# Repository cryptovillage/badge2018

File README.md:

# badge2018

To buld the ESP32 firmware:

1. Install the ESP32 toolchain for your OS. You do not need to install the ESP-IDF -- that happens automatically in the next step.
  * For Linux: https://esp-idf.readthedocs.io/en/v3.2/get-started/linux-setup.html
  * For Windows: https://esp-idf.readthedocs.io/en/v3.2/get-started/windows-setup.html
  * For OSX: https://esp-idf.readthedocs.io/en/v3.2/get-started/macos-setup.html

2. Pull in the ESP-IDF, MicroPython, and other dependencies:
`git submodule update --init --recursive`

3. Build mpy_cross:
`cd firmware/esp32/components/micropython/micropython/mpy-cross/ && make && cd ../../../..`

4. Optionally configure the serial port that your badge appears on (under Serial Flasher Config):
`make menuconfig`

5. Build it:
`make -j5`

6. Flash it:
`make flash`

The EFM8 firmware has only been built inside Simplicity Studio.

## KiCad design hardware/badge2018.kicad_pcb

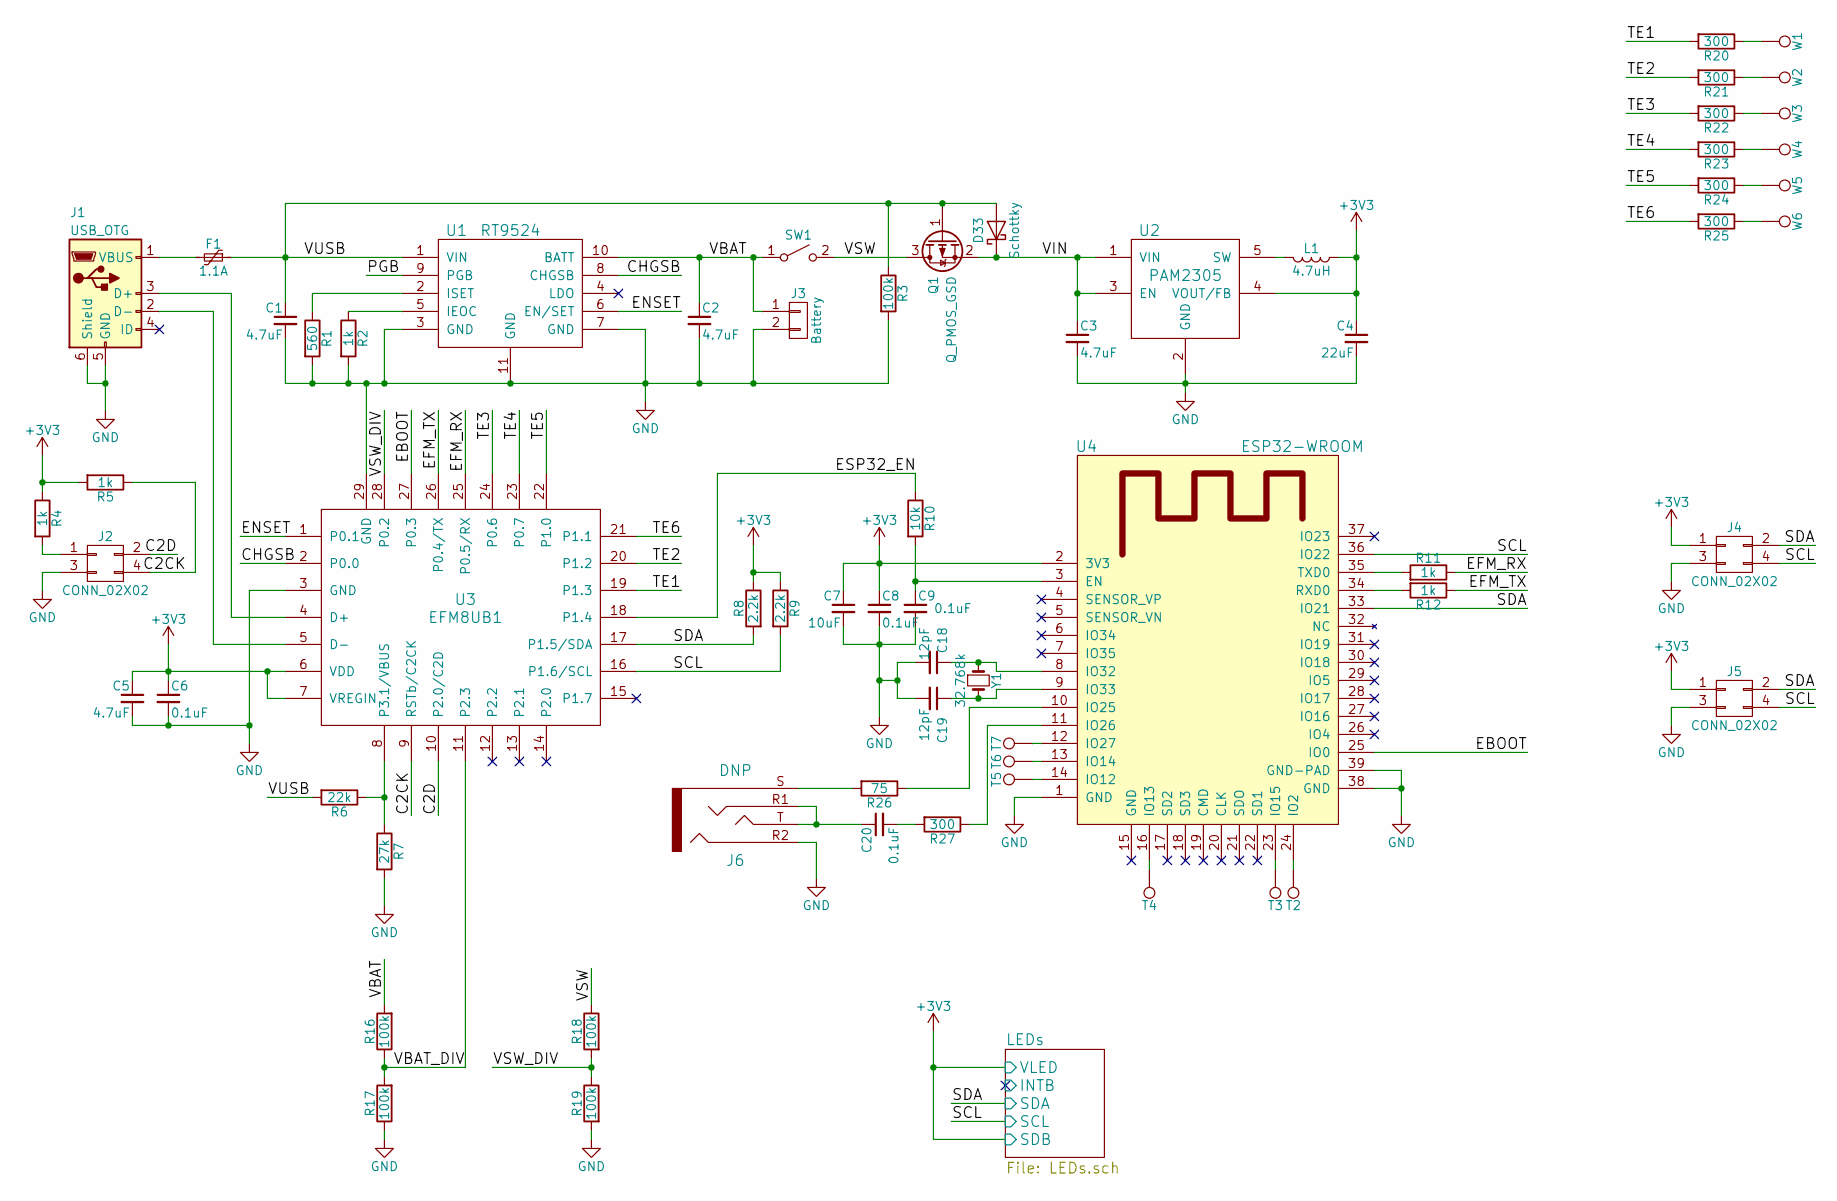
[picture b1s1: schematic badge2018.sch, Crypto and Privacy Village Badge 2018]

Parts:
C1, C2, C3, C5: 4.7uF; C_0603; Tolerance +/- 10%; Voltage 10V
C4: 22uF; C_0603; Tolerance +/- 10%; Voltage 10V
C6, C8, C9: 0.1uF; C_0603; Tolerance +/- 10%; Voltage 6.3V
C7: 10uF; C_0603; Tolerance +/- 10%; Voltage 10V
C18, C19: 12pF; C_0603; Tolerance +/- 10%; Voltage 6.3V
C20: 0.1uF; C_0603; Tolerance +/- 10%; Voltage 10V
D33: Schottky; D_SOD-323; MfgPartNum BAT20JFILM
F1: 1.1A; R_1210; Voltage 6V; MfgPartNum MF-USMF110-2
J1: USB_OTG; USB_Micro-B-cpv; MfgPartNum 10118192-0001LF
J2: CONN_02X02; Socket_Strip_Straight_2x02_TP
J3: Battery; JST_PH_SMD; MfgPartNum S2B-PH-SM4-TB(LF)(SN)
J4, J5: CONN_02X02; DC26_Shitty_Addon
J6: DNP; TRRS_jack; MfgPartNum SJ-43516-SMT-TR
L1: 4.7uH; R_0805
Q1: Q_PMOS_GSD; SOT-23; Voltage 30V; MfgPartNum DMG2307L-7
R1: 560; R_0603; Tolerance 1%
R2: 1k; R_0603; Tolerance 1%
R3: 100k; R_0603; Tolerance 5%
R4, R5, R11, R12: 1k; R_0603; Tolerance 5%
R6: 22k; R_0603; Tolerance 5%
R7: 27k; R_0603; Tolerance 5%
R8, R9: 2.2k; R_0603; Tolerance 5%
R10: 10k; R_0603; Tolerance 5%
R16, R17, R18, R19: 100k; R_0603; Tolerance 1%
R20, R21, R22, R23, R24: 300; R_0603; Tolerance 5%
R25, R27: 300; R_0603; Tolerance 1%
R26: 75; R_0603; Tolerance 1%
SW1: SPST; DPDT_SMD; Voltage 6V; MfgPartNum JS202011SCQN
T2, T3, T4, T5, T6, T7: TP; Measurement_Point_Round-SMD-Pad_Small
U1: RT9524; DFN-10-1EP_2x3mm_Pitch0.5mm; MfgPartNum RT9524GQW
U2: PAM2305; SOT-23-5; MfgPartNum PAM2305AAB330
U3: EFM8UB1; QFN-28-1EP_5x5mm_Pitch0.5mm; MfgPartNum EFM8UB10F16G-C-QFN28
U4: ESP32-WROOM; MfgPartNum ESP-WROOM-32
W1, W2, W3, W4, W5, W6: TP; Measurement_Point_Round-SMD-Pad_Small
Y1: 32.768k; abs25_crystal; MfgPartNum ABS25-32.768KHZ-T

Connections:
+3V3: C4.1, C5.1, C6.1, C7.1, C8.1, J4.1, J5.1, L1.1, R4.1, R5.2, R8.1, R9.1, U2.4 (VOUT/FB), U3.6 (VDD), U3.7 (VREGIN), U4.2 (3V3); also elsewhere on the board
/C2CK: J2.4, R5.1, U3.9 (RSTb/C2CK)
/C2D: J2.2, U3.10 (P2.0/C2D)
/CHGSB: U1.8 (CHGSB), U3.2 (P0.0)
/EBOOT: U3.27 (P0.3), U4.25 (IO0)
/EFM_RX: R11.1, U3.25 (P0.5/RX)
/EFM_TX: R12.1, U3.26 (P0.4/TX)
/ENSET: U1.6 (EN/SET), U3.1 (P0.1)
/ESP32_EN: R10.1, U3.18 (P1.4)
/PGB: U1.9 (PGB)
/SCL: J4.4, J5.4, R9.2, U3.16 (P1.6/SCL), U4.36 (IO22); also elsewhere on the board
/SDA: J4.2, J5.2, R8.2, U3.17 (P1.5/SDA), U4.33 (IO21); also elsewhere on the board
/TE1: R20.2, U3.19 (P1.3)
/TE2: R21.2, U3.20 (P1.2)
/TE3: R22.2, U3.24 (P0.6)
/TE4: R23.2, U3.23 (P0.7)
/TE5: R24.2, U3.22 (P1.0)
/TE6: R25.2, U3.21 (P1.1)
/VBAT: C2.1, J3.1, R16.2, SW1.1 (A), U1.10 (BATT)
/VBAT_DIV: R16.1, R17.2, U3.11 (P2.3)
/VIN: C3.1, D33.1 (K), Q1.2 (S), U2.1 (VIN), U2.3 (EN)
/VSW: Q1.3 (D), R18.1, SW1.2 (B)
/VSW_DIV: R18.2, R19.1, U3.28 (P0.2)
/VUSB: C1.1, D33.2 (A), F1.1, Q1.1 (G), R3.1, R6.2, U1.1 (VIN)
GND: C1.2, C2.2, C3.2, C4.2, C5.2, C6.2, C7.2, C8.2, C9.2, C18.2, C19.2, J1.5 (GND), J1.6 (Shield), J2.3, J3.2, J4.3, J5.3, J6.R2, R1.2, R2.2, R3.2, R7.2, R17.1, R19.2, U1.3 (GND), U1.7 (GND), U1.11 (GND), U2.2 (GND), U3.3 (GND), U3.29 (GND), U4.1 (GND), U4.38 (GND), U4.39 (GND-PAD); also elsewhere on the board
unnamed: C9.1, R10.2, U4.3 (EN)
unnamed: C18.1, U4.8 (IO32), Y1.1
unnamed: C19.1, U4.9 (IO33), Y1.2
unnamed: C20.1, J6.R1, J6.T
unnamed: C20.2, R27.2
unnamed: F1.2, J1.1 (VBUS)
unnamed: J1.2 (D-), U3.5 (D-)
unnamed: J1.3 (D+), U3.4 (D+)
unnamed: J2.1, R4.2
unnamed: J6.S, R26.2
unnamed: L1.2, U2.5 (SW)
unnamed: R1.1, U1.2 (ISET)
unnamed: R2.1, U1.5 (IEOC)
unnamed: R6.1, R7.1, U3.8 (P3.1/VBUS)
unnamed: R11.2, U4.35 (TXD0)
unnamed: R12.2, U4.34 (RXD0)
unnamed: R20.1, W1.1
unnamed: R21.1, W2.1
unnamed: R22.1, W3.1
unnamed: R23.1, W4.1
unnamed: R24.1, W5.1
unnamed: R25.1, W6.1
unnamed: R26.1, U4.10 (IO25)
unnamed: R27.1, U4.11 (IO26)
unnamed: T2.1, U4.24 (IO2)
unnamed: T3.1, U4.23 (IO15)
unnamed: T4.1, U4.16 (IO13)
unnamed: T5.1, U4.14 (IO12)
unnamed: T6.1, U4.13 (IO14)
unnamed: T7.1, U4.12 (IO27)

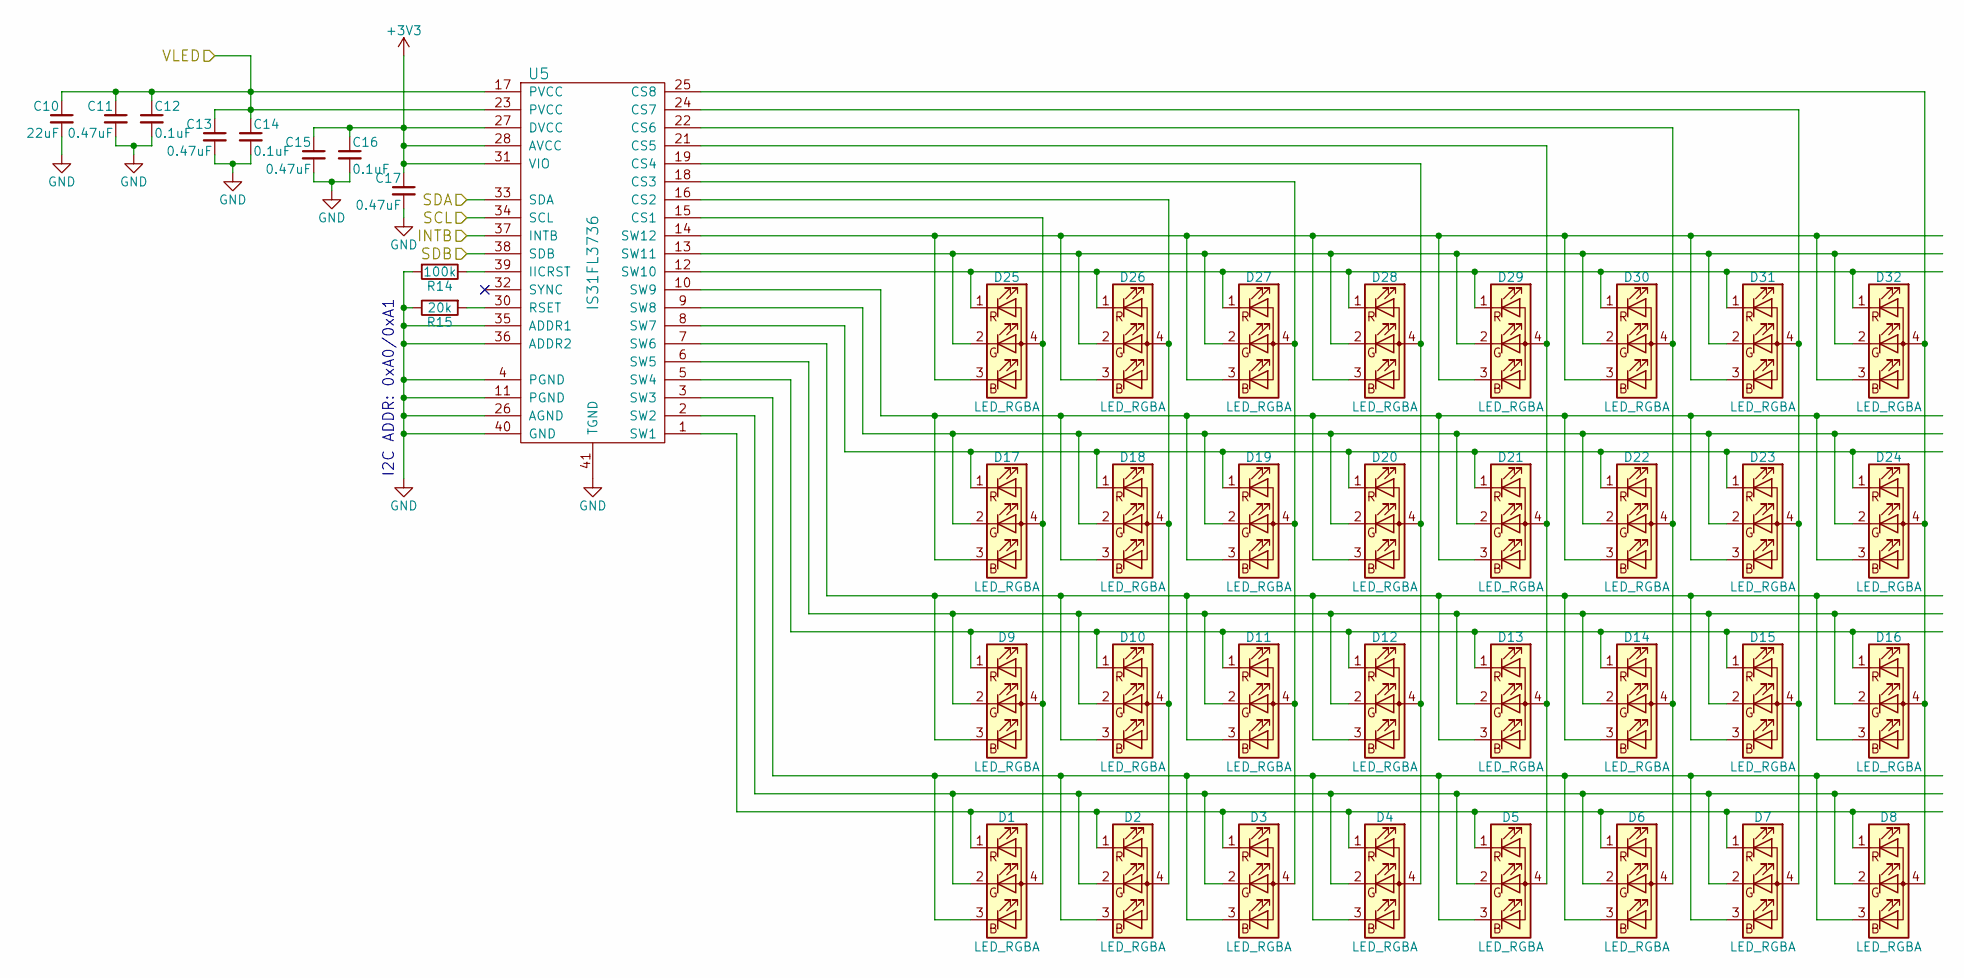
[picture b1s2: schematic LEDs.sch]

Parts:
C10: 22uF; C_0603; Tolerance +/- 10%; Voltage 10V
C11, C13, C15, C17: 0.47uF; C_0603; Tolerance +/- 10%; Voltage 6.3V
C12, C14, C16: 0.1uF; C_0603; Tolerance +/- 10%; Voltage 6.3V
D1, D2, D3, D4, D5, D6, D7, D8, D9, D10, D11, D12, D13, D14, D15, D16, D17, D18, D19, D20, D21, D22, D23, D24, D25, D26, D27, D28, D29, D30, D31, D32: LED_RGBA; RGBC_LED
R14: 100k; R_0603; Tolerance 0.05
R15: 20k; R_0603; Tolerance 0.01
U5: IS31FL3736; QFN-40-1EP_5x5mm_Pitch0.4mm

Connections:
+3V3: C10.1, C11.1, C12.1, C13.1, C14.1, C15.1, C16.1, C17.1, U5.17 (PVCC), U5.23 (PVCC), U5.27 (DVCC), U5.28 (AVCC), U5.31 (VIO), U5.38 (SDB); also elsewhere on the board
/LEDs/INTB: U5.37 (INTB)
/SCL: U5.34 (SCL); also elsewhere on the board
/SDA: U5.33 (SDA); also elsewhere on the board
GND: C10.2, C11.2, C12.2, C13.2, C14.2, C15.2, C16.2, C17.2, R14.2, R15.1, U5.4 (PGND), U5.11 (PGND), U5.26 (AGND), U5.35 (ADDR1), U5.36 (ADDR2), U5.40 (GND), U5.41 (TGND); also elsewhere on the board
unnamed: D1.1 (RK), D2.1 (RK), D3.1 (RK), D4.1 (RK), D5.1 (RK), D6.1 (RK), D7.1 (RK), D8.1 (RK), U5.1 (SW1)
unnamed: D1.2 (GK), D2.2 (GK), D3.2 (GK), D4.2 (GK), D5.2 (GK), D6.2 (GK), D7.2 (GK), D8.2 (GK), U5.2 (SW2)
unnamed: D1.3 (BK), D2.3 (BK), D3.3 (BK), D4.3 (BK), D5.3 (BK), D6.3 (BK), D7.3 (BK), D8.3 (BK), U5.3 (SW3)
unnamed: D1.4 (A), D9.4 (A), D17.4 (A), D25.4 (A), U5.15 (CS1)
unnamed: D9.1 (RK), D10.1 (RK), D11.1 (RK), D12.1 (RK), D13.1 (RK), D14.1 (RK), D15.1 (RK), D16.1 (RK), U5.5 (SW4)
unnamed: D9.2 (GK), D10.2 (GK), D11.2 (GK), D12.2 (GK), D13.2 (GK), D14.2 (GK), D15.2 (GK), D16.2 (GK), U5.6 (SW5)
unnamed: D9.3 (BK), D10.3 (BK), D11.3 (BK), D12.3 (BK), D13.3 (BK), D14.3 (BK), D15.3 (BK), D16.3 (BK), U5.7 (SW6)
unnamed: D2.4 (A), D10.4 (A), D18.4 (A), D26.4 (A), U5.16 (CS2)
unnamed: D3.4 (A), D11.4 (A), D19.4 (A), D27.4 (A), U5.18 (CS3)
unnamed: D4.4 (A), D12.4 (A), D20.4 (A), D28.4 (A), U5.19 (CS4)
unnamed: D5.4 (A), D13.4 (A), D21.4 (A), D29.4 (A), U5.21 (CS5)
unnamed: D6.4 (A), D14.4 (A), D22.4 (A), D30.4 (A), U5.22 (CS6)
unnamed: D7.4 (A), D15.4 (A), D23.4 (A), D31.4 (A), U5.24 (CS7)
unnamed: D8.4 (A), D16.4 (A), D24.4 (A), D32.4 (A), U5.25 (CS8)
unnamed: D17.1 (RK), D18.1 (RK), D19.1 (RK), D20.1 (RK), D21.1 (RK), D22.1 (RK), D23.1 (RK), D24.1 (RK), U5.8 (SW7)
unnamed: D17.2 (GK), D18.2 (GK), D19.2 (GK), D20.2 (GK), D21.2 (GK), D22.2 (GK), D23.2 (GK), D24.2 (GK), U5.9 (SW8)
unnamed: D17.3 (BK), D18.3 (BK), D19.3 (BK), D20.3 (BK), D21.3 (BK), D22.3 (BK), D23.3 (BK), D24.3 (BK), U5.10 (SW9)
unnamed: D25.1 (RK), D26.1 (RK), D27.1 (RK), D28.1 (RK), D29.1 (RK), D30.1 (RK), D31.1 (RK), D32.1 (RK), U5.12 (SW10)
unnamed: D25.2 (GK), D26.2 (GK), D27.2 (GK), D28.2 (GK), D29.2 (GK), D30.2 (GK), D31.2 (GK), D32.2 (GK), U5.13 (SW11)
unnamed: D25.3 (BK), D26.3 (BK), D27.3 (BK), D28.3 (BK), D29.3 (BK), D30.3 (BK), D31.3 (BK), D32.3 (BK), U5.14 (SW12)
unnamed: R14.1, U5.39 (IICRST)
unnamed: R15.2, U5.30 (RSET)

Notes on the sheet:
I2C ADDR: 0xA0/0xA1

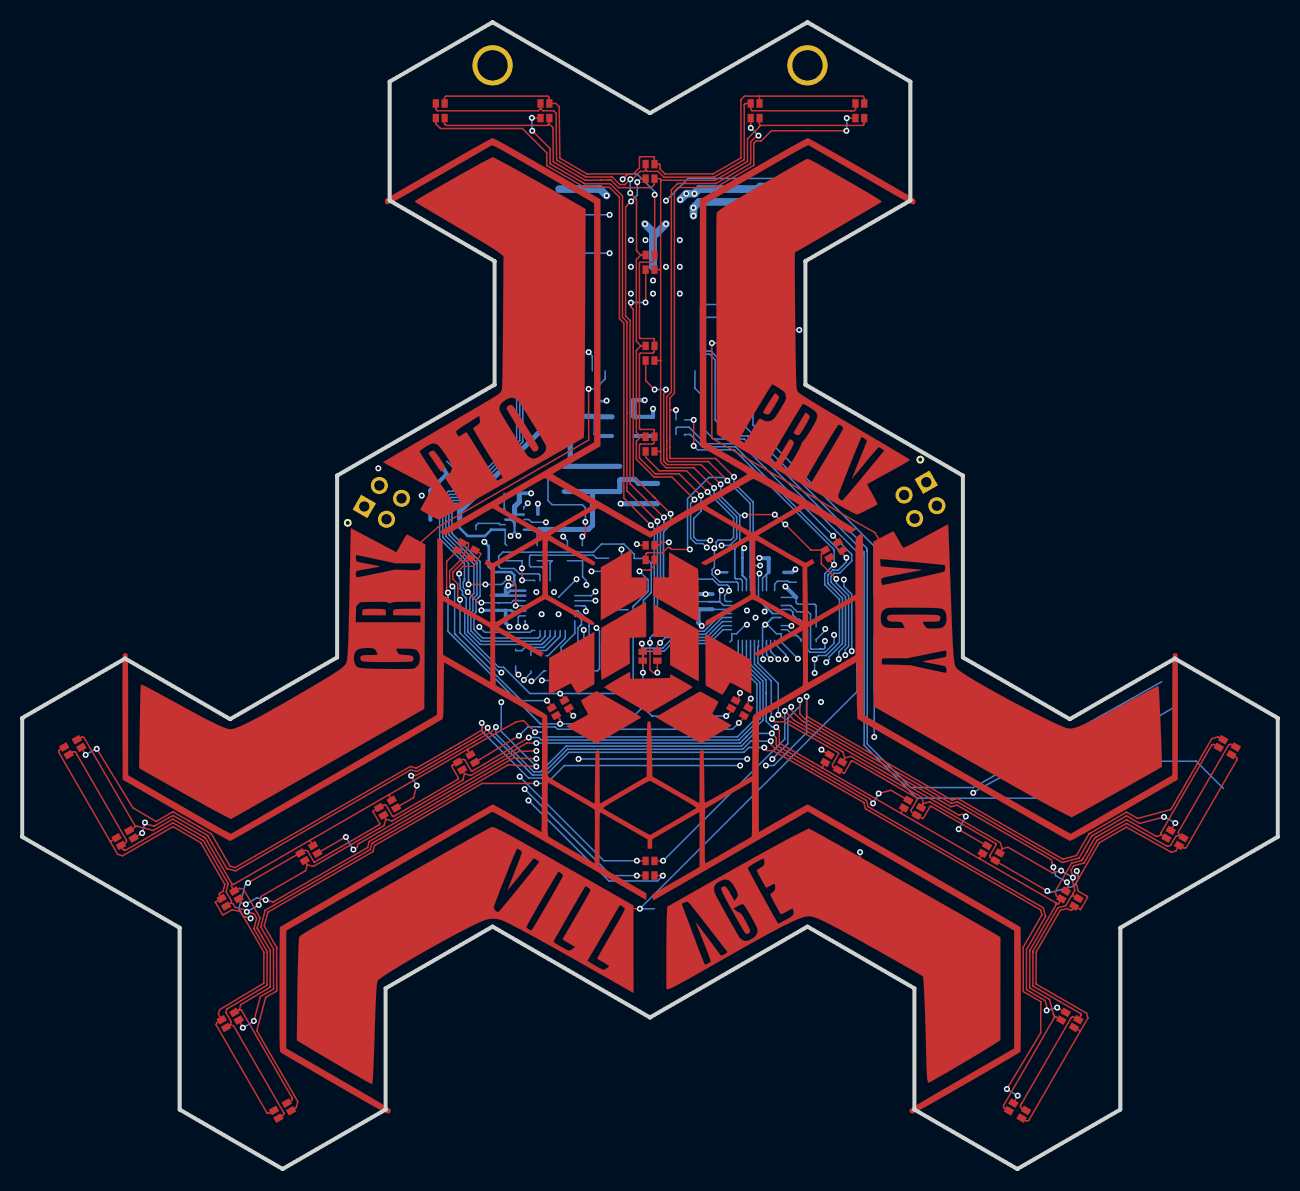
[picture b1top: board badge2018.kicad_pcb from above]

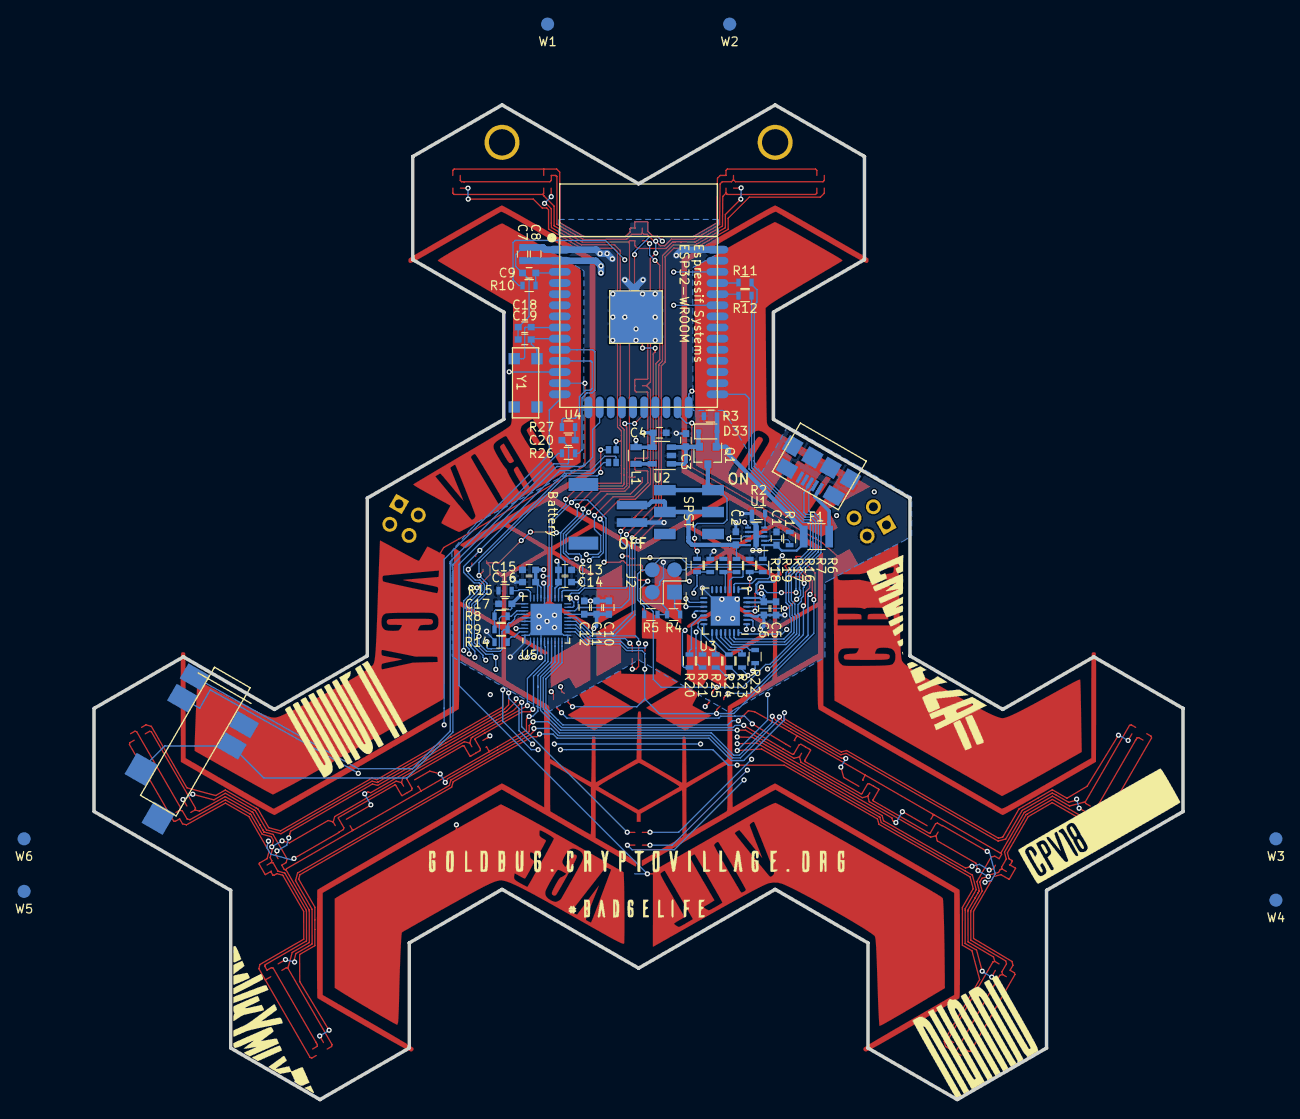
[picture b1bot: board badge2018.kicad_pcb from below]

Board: 4 copper layers, 124.3 x 113.5 mm, 112 parts (68 on the bottom side), 76 nets.

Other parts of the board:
ART1: COPPER; copperfrontfixedFCu
ART2: MASK; copperfrontfixedFMask
Battery: LP803860
hole_l: hole
hole_l#2: hole

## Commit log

2018-08-10 Initial commit of v1.0
2019-06-02 Update .gitmodules to point to cpv micropython repo
2019-06-09 Bump esp-idf to v3.2
